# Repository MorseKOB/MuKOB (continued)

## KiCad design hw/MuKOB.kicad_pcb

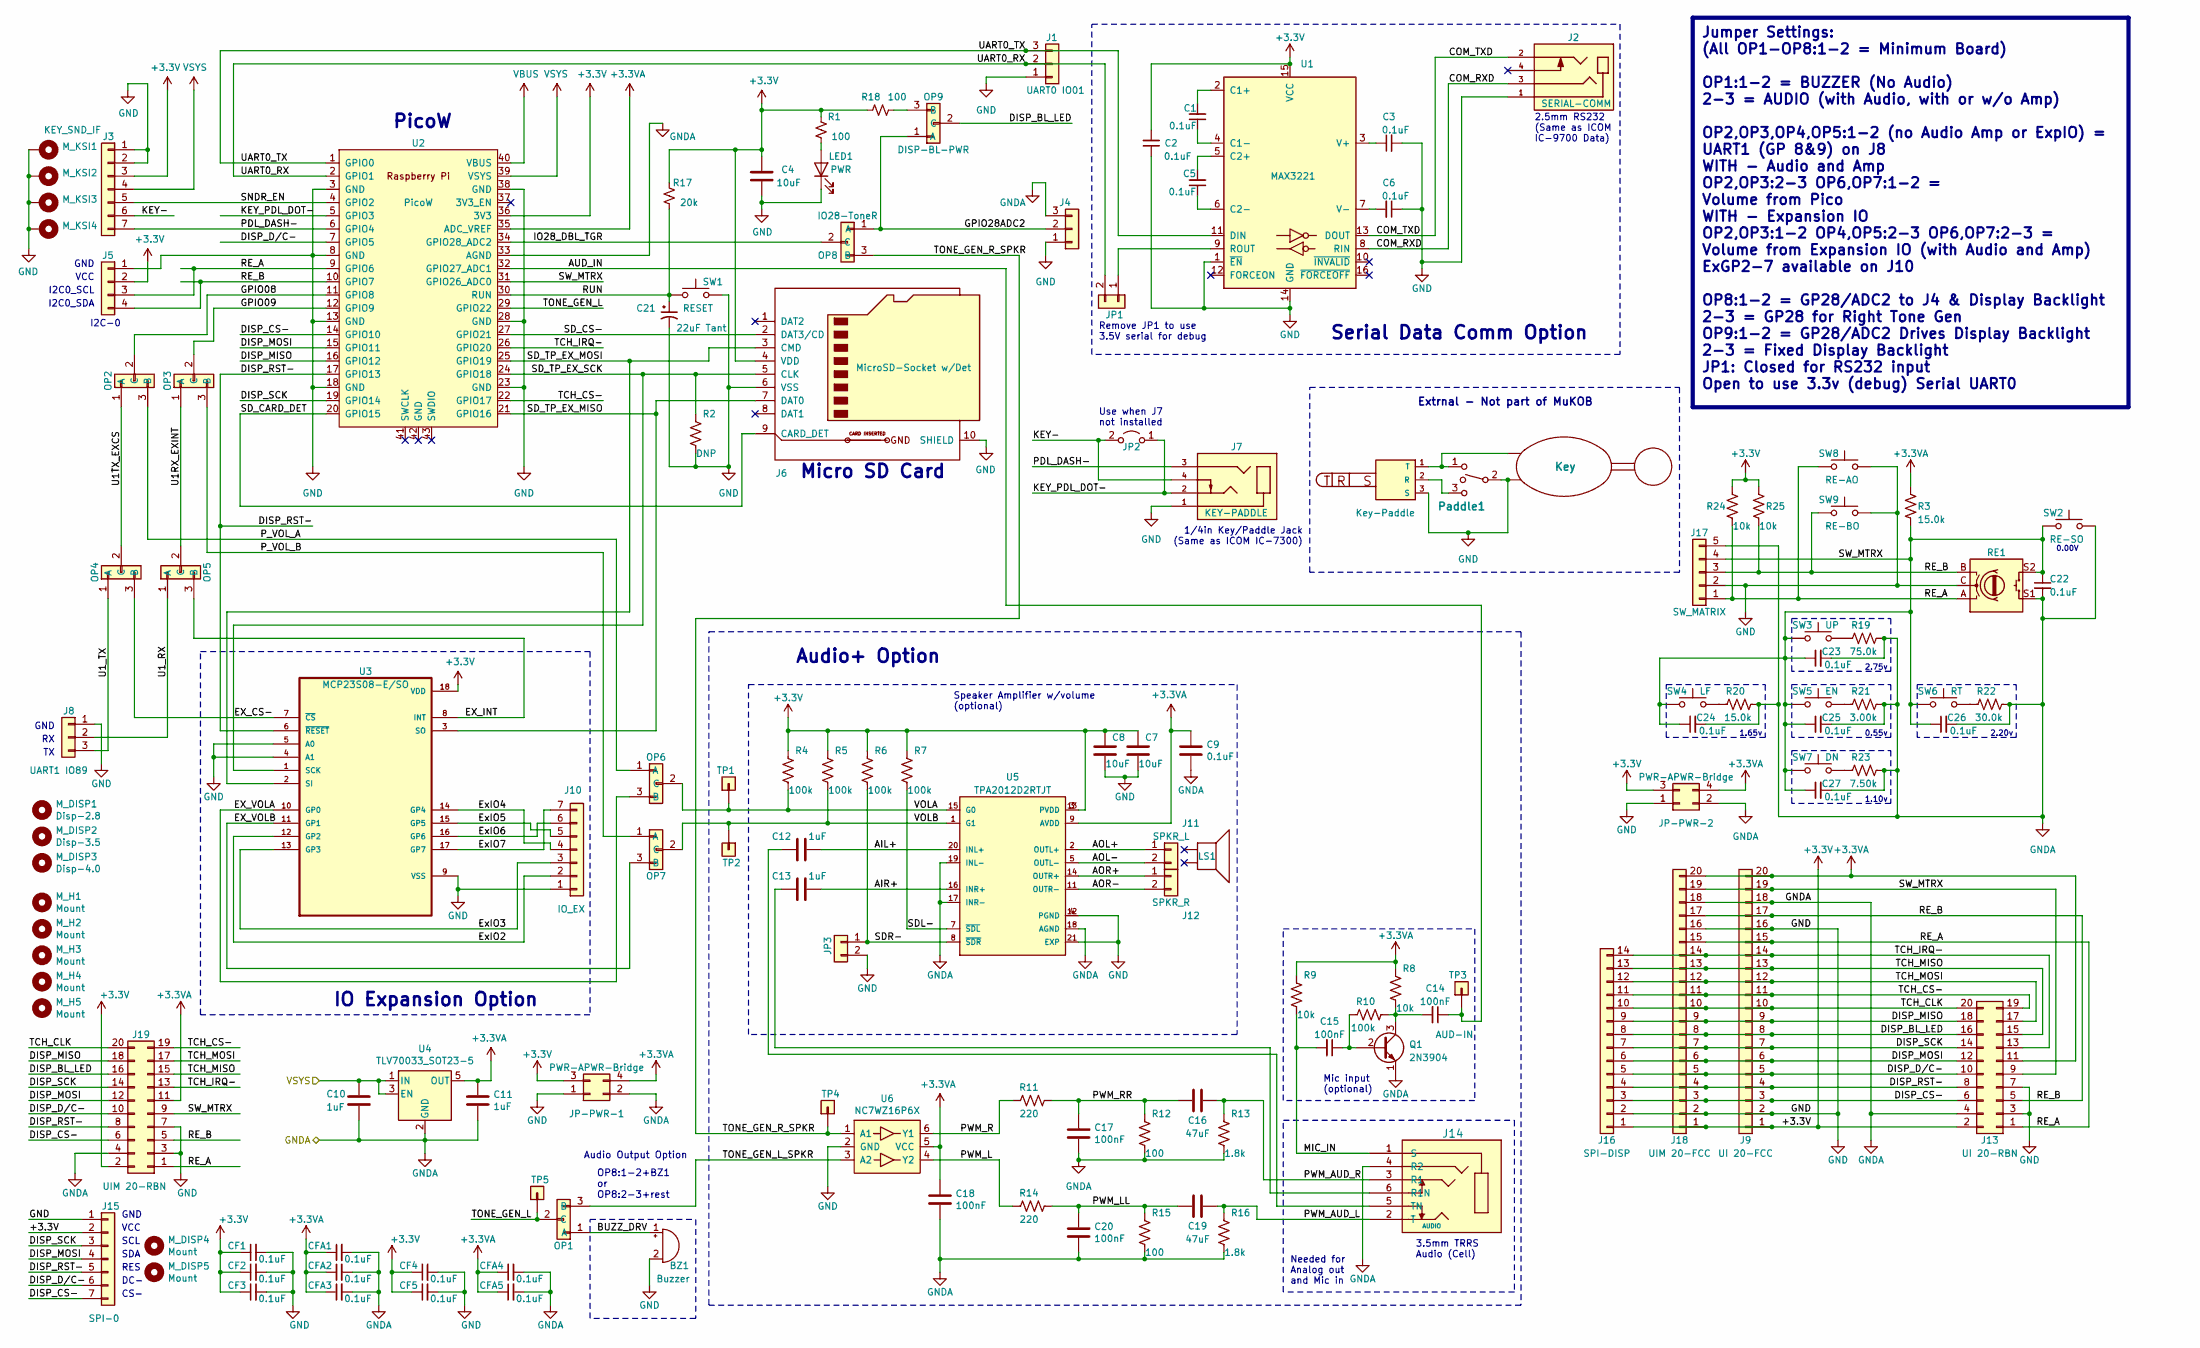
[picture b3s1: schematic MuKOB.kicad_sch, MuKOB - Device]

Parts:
BZ1: Buzzer; Buzzer_12x9.5RM7.6
C1, C2, C3, C5, C6, C9, C22, C23, C24, C25, C26, C27: 0.1uF; C_0603_1608Metric_Pad1.08x0.95mm_HandSolder
C4, C7, C8: 10uF; C_0603_1608Metric
C10, C11, C12, C13: 1uF; C_0201_0603Metric_Pad0.64x0.40mm_HandSolder
C14, C15, C17, C18, C20: 100nF; C_0201_0603Metric_Pad0.64x0.40mm_HandSolder
C16, C19: 47uF; C_1206_3216Metric_Pad1.33x1.80mm_HandSolder
C21: 22uF Tant; CP_EIA-3528-15_AVX-H_Pad1.50x2.35mm_HandSolder
CF1, CF2, CF3, CF4, CF5: 0.1uF; C_Axial_L3.8mm_D2.6mm_P7.50mm_Horizontal
CFA1, CFA2, CFA3, CFA4, CFA5: 0.1uF; C_Axial_L3.8mm_D2.6mm_P7.50mm_Horizontal
J1: UART0 IO01; PinHeader_1x03_P2.54mm_Vertical
J2: SERIAL-COMM; CUI_SJ-2524-SMT-TRS-audio-jack; PARTREV 1.05
J3: KEY_SND_IF; PinSocket_1x07_P2.54mm_Vertical
J4: GPIO28; PinHeader_1x03_P2.54mm_Vertical
J5: I2C-0; PinSocket_1x04_P2.54mm_Vertical
J6: MicroSD-Socket w/Det; SDCard-GCT_MEM2075-00-140-01-A
J7: KEY-PADDLE; CUI_SJ-63063B-audio-jack; PARTREV 1.0
J8: UART1 IO89; PinHeader_1x03_P2.54mm_Vertical
J9: UI 20-FCC; Amphenol_F51L_1x20_P1.00mm_Horizontal-FFC
J10: IO_EX; PinHeader_1x07_P2.54mm_Vertical
J11: SPKR_L; TerminalBlock_Philmore_TB132_1x02_P5.00mm_Horizontal
J12: SPKR_R; TerminalBlock_Philmore_TB132_1x02_P5.00mm_Horizontal
J13: UI 20-RBN; PinHeader_2x10_P2.54mm_Vertical
J14: AUDIO; CUI_DEVICES_SJ43516_SMT-CPJ
J15: SPI-0; PinSocket_1x07_P2.54mm_Vertical
J16: SPI-DISP; PinSocket_1x14_P2.54mm_Vertical
J17: SW_MATRIX; PinHeader_1x05_P2.54mm_Vertical
J18: UIM 20-FCC; Amphenol_F51L_1x20_P1.00mm_Horizontal-FFC
J19: UIM 20-RBN; PinHeader_2x10_P2.54mm_Vertical
J-SP1: Key-Paddle
JP1: S0-RX; PinHeader_1x02_P2.54mm_Vertical
JP2: J7-BP; PinHeader_1x02_P2.54mm_Vertical
JP3: AUD-SDR-; PinHeader_1x02_P2.54mm_Vertical
JP-PWR-1, JP-PWR-2: PWR-APWR-Bridge; PinHeader_2x02_P2.54mm_Vertical
KEY-EXT1: Key
LED1: PWR; LED_SMD_SIDEVIEW_Harvatek
LS1: Speaker
M_DISP1: Disp-2.8; MountingHole_3.2mm_M3
M_DISP2: Disp-3.5; MountingHole_3.2mm_M3
M_DISP3: Disp-4.0; MountingHole_3.2mm_M3
M_DISP4, M_DISP5: Mount; MountingHole_2.7mm_M2.5
M_H1, M_H2, M_H3, M_H4, M_H5: Mount; MountingHole_3.2mm_M3_ISO7380
M_KSI1, M_KSI2, M_KSI3, M_KSI4: MountingHole_Pad; MountingHole_3.2mm_M3_ISO7380_Pad_TopBottom
OP1: BZ-SPK; PinHeader_1x03_P2.54mm_Vertical
OP2, OP3, OP4, OP5, OP6, OP7: OP_A-B; PinHeader_1x03_P2.54mm_Vertical
OP8: IO28-ToneR; PinHeader_1x03_P2.54mm_Vertical
OP9: DISP-BL-PWR; PinHeader_1x03_P2.54mm_Vertical
Paddle1: PDL_EXT
Q1: 2N3904; TO-92_Inline
R1, R12, R15, R18: 100; R_0402_1005Metric_Pad0.72x0.64mm_HandSolder
R2: DNP; R_Axial_DIN0207_L6.3mm_D2.5mm_P10.16mm_Horizontal
R3, R20: 15.0k; R_0402_1005Metric_Pad0.72x0.64mm_HandSolder
R4, R5, R6, R7, R10: 100k; R_0402_1005Metric_Pad0.72x0.64mm_HandSolder
R8, R9, R24, R25: 10k; R_0402_1005Metric_Pad0.72x0.64mm_HandSolder
R11, R14: 220; R_0402_1005Metric_Pad0.72x0.64mm_HandSolder
R13, R16: 1.8k; R_0402_1005Metric_Pad0.72x0.64mm_HandSolder
R17: 20k; R_0402_1005Metric_Pad0.72x0.64mm_HandSolder
R19: 75.0k; R_0402_1005Metric_Pad0.72x0.64mm_HandSolder
R21: 3.00k; R_0402_1005Metric_Pad0.72x0.64mm_HandSolder
R22: 30.0k; R_0402_1005Metric_Pad0.72x0.64mm_HandSolder
R23: 7.50k; R_0402_1005Metric_Pad0.72x0.64mm_HandSolder
RE1: RotEnc-SW; RotaryEncoder_Bourns_Vertical_PEC12R-3xxxF-Sxxxx
SW1: RESET; SW_PUSH_SMD_1P1T_NO_45x45mm-CK
SW2: RE-SO; SW_PUSH_SMD_1P1T_NO_45x45mm-CK
SW3: UP; SW_PUSH_SMD_1P1T_NO_45x45mm-CK
SW4: LF; SW_PUSH_SMD_1P1T_NO_45x45mm-CK
SW5: EN; SW_PUSH_SMD_1P1T_NO_45x45mm-CK
SW6: RT; SW_PUSH_SMD_1P1T_NO_45x45mm-CK
SW7: DN; SW_PUSH_SMD_1P1T_NO_45x45mm-CK
SW8: RE-AO; SW_PUSH_SMD_1P1T_NO_45x45mm-CK
SW9: RE-BO; SW_PUSH_SMD_1P1T_NO_45x45mm-CK
TP1: VOL-A; PinHeader_1x01_P2.54mm_Vertical
TP2: VOL-B; PinHeader_1x01_P2.54mm_Vertical
TP3: AUD-IN; PinHeader_1x01_P2.54mm_Vertical
TP4: TONE-R; PinHeader_1x01_P2.54mm_Vertical
TP5: TONE-L; PinHeader_1x01_P2.54mm_Vertical
U1: MAX3221; TSSOP-16
U2: PicoW; RPi_PicoW_SMD_TH
U3: MCP23S08-E/SO; SOIC-18W_7.5x11.6mm_P1.27mm
U4: TLV70033_SOT23-5; SOT-23-5
U5: TPA2012D2RTJT; QFN50P400X400X80-21N270X270; PARTREV NA
U6: NC7WZ16P6X; SOT-363_SC-70-6

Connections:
+3.3V: C2.2, C4.1, C7.1, C8.1, CF1.1, CF2.1, CF3.1, CF4.1, CF5.1, J3.3, J5.2, J6.4 (VDD), J9.1, J13.2, J15.2, J16.1, J18.1, J19.2, JP-PWR-1.3, JP-PWR-2.3, R1.1, R4.1, R5.1, R6.1, R7.1, R17.1, R18.1, R24.1, R25.1, U1.15 (VCC), U2.36 (3V3), U3.18 (VDD), U5.3 (PVDD), U5.13 (PVDD)
+3.3VA: C9.1, C11.1, C18.1, CFA1.1, CFA2.1, CFA3.1, CFA4.1, CFA5.1, J9.20, J13.11, J18.20, J19.11, JP-PWR-1.4, JP-PWR-2.4, R3.1, R8.1, R9.1, U2.35 (ADC_VREF), U4.5 (OUT), U5.9 (AVDD), U6.5 (VCC)
/AIL+: C12.1, U5.20 (INL+)
/AIR+: C13.1, U5.16 (INR+)
/AOL+: J11.1, U5.2 (OUTL+)
/AOL-: J11.2, U5.5 (OUTL-)
/AOR+: J12.1, U5.14 (OUTR+)
/AOR-: J12.2, U5.11 (OUTR-)
/AUD_IN: C14.1, TP3.1, U2.32 (GPIO27_ADC1)
/BUZZ_DRV: BZ1.1 (-), OP1.1 (A)
/COM_RXD: J2.3, U1.8 (RIN)
/COM_TXD: J2.2, U1.13 (DOUT)
/DISP_BL_LED: J9.8, J13.16, J16.8, J18.8, J19.16, OP9.2 (C)
/DISP_CS-: J9.3, J13.6, J15.7, J16.3, J18.3, J19.6, U2.14 (GPIO10)
/DISP_D/C-: J9.5, J13.10, J15.6, J16.5, J18.5, J19.10, U2.7 (GPIO5)
/DISP_MISO: J9.9, J13.18, J16.9, J18.9, J19.18, U2.16 (GPIO12)
/DISP_MOSI: J9.6, J13.12, J15.4, J16.6, J18.6, J19.12, U2.15 (GPIO11)
/DISP_RST-: J9.4, J13.8, J15.5, J16.4, J18.4, J19.8, U2.17 (GPIO13), U3.6 (~RESET)
/DISP_SCK: J9.7, J13.14, J15.3, J16.7, J18.7, J19.14, U2.19 (GPIO14)
/EX_CS-: OP4.3 (B), U3.7 (~CS)
/EX_INT: OP5.3 (B), U3.8 (INT)
/EX_VOLA: OP6.3 (B), U3.10 (GP0)
/EX_VOLB: OP7.3 (B), U3.11 (GP1)
/ExIO2: J10.2, U3.12 (GP2)
/ExIO3: J10.3, U3.13 (GP3)
/ExIO4: J10.4, U3.14 (GP4)
/ExIO5: J10.5, U3.15 (GP5)
/ExIO6: J10.6, U3.16 (GP6)
/ExIO7: J10.7, U3.17 (GP7)
/GPIO08: OP2.2 (C), U2.11 (GPIO8)
/GPIO09: OP3.2 (C), U2.12 (GPIO9)
/GPIO28ADC2: J4.2, OP8.1 (A), OP9.1 (A)
/IO28_DBL_TGR: OP8.2 (C), U2.34 (GPIO28_ADC2)
/KEY-: J3.6, J7.4, JP2.2 (B)
/KEY_PDL_DOT-: J7.2, JP2.1 (A), U2.5 (GPIO3)
/MIC_IN: C15.2, J14.1 (S), R9.2
/PDL_DASH-: J3.7, J7.3, U2.6 (GPIO4)
/PWM_AUD_L: C19.1, J14.2 (T), R16.1
/PWM_AUD_R: C16.1, J14.3 (R1), R13.1
/PWM_L: R14.2, U6.4 (Y2)
/PWM_LL: C19.2, C20.1, R14.1, R15.1
/PWM_R: R11.2, U6.6 (Y1)
/PWM_RR: C16.2, C17.1, R11.1, R12.1
/P_VOL_A: OP2.3 (B), OP6.1 (A)
/P_VOL_B: OP3.3 (B), OP7.1 (A)
/RE_A: J5.3, J9.15, J13.1, J17.1, J18.15, J19.1, R24.2, RE1.A, SW8.1, U2.9 (GPIO6)
/RE_B: J5.4, J9.17, J13.5, J17.3, J18.17, J19.5, R25.2, RE1.B, SW9.1, U2.10 (GPIO7)
/RUN: C21.1, R17.2, SW1.1, U2.30 (RUN)
/SDL-: R7.2, U5.7 (~SDL)
/SDR-: JP3.1, R6.2, U5.8 (~SDR)
/SD_CARD_DET: J6.9 (CARD_DET), U2.20 (GPIO15)
/SD_CS-: J6.2 (DAT3/CD), U2.27 (GPIO21)
/SD_TP_EX_MISO: J6.7 (DAT0), U2.21 (GPIO16), U3.3 (SO)
/SD_TP_EX_SCK: J6.5 (CLK), J-SP1.1 (T), Paddle1.1, R2.1, U2.24 (GPIO18), U3.1 (SCK)
/SNDR_EN: J3.5, U2.4 (GPIO2)
/SW_MTRX: C22.1, C23.1, C24.1, C25.1, C26.1, C27.1, J9.19, J13.9, J17.4, J18.19, J19.9, R3.2, RE1.S2, SW2.1, SW3.1, SW4.1, SW5.1, SW6.1, SW7.1, U2.31 (GPIO26_ADC0)
/TCH_CLK: J9.10, J13.20, J16.10, J18.10, J19.20
/TCH_CS-: J9.11, J13.19, J16.11, J18.11, J19.19, U2.22 (GPIO17)
/TCH_IRQ-: J9.14, J13.13, J16.14, J18.14, J19.13, U2.26 (GPIO20)
/TCH_MISO: J9.13, J13.15, J16.13, J18.13, J19.15
/TCH_MOSI: J9.12, J13.17, J16.12, J18.12, J19.17
/TONE_GEN_L: OP1.2 (C), TP5.1, U2.29 (GPIO22)
/TONE_GEN_L_SPKR: OP1.3 (B), U6.3 (A2)
/TONE_GEN_R_SPKR: OP8.3 (B), TP4.1, U6.1 (A1)
/U1RX_EXINT: OP3.1 (A), OP5.2 (C)
/U1TX_EXCS: OP2.1 (A), OP4.2 (C)
/U1_RX: J8.2, OP5.1 (A)
/U1_TX: J8.3, OP4.1 (A)
/UART0_RX: J1.2, JP1.2, U2.2 (GPIO1)
/UART0_TX: J1.3, U1.11 (DIN), U2.1 (GPIO0)
/VOLA: OP6.2 (C), R4.2, TP1.1, U5.15 (G0)
/VOLB: OP7.2 (C), R5.2, TP2.1, U5.1 (G1)
GNDA: C9.2, C10.2, C11.2, C17.2, C18.2, C20.2, C22.2, C23.2, C24.2, C25.2, C26.2, C27.2, CFA1.2, CFA2.2, CFA3.2, CFA4.2, CFA5.2, J4.3, J9.18, J13.4, J14.4 (R2), J17.5, J18.18, J19.4, JP-PWR-1.2, JP-PWR-2.2, Q1.1 (E), R12.2, R13.2, R15.2, R16.2, R19.1, R20.1, R21.1, R22.1, R23.1, RE1.S1, SW2.2, U2.33 (AGND), U4.2 (GND), U5.17 (INR-), U5.18 (AGND), U5.19 (INL-)
unnamed: C13.2, J14.6 (R1N)
unnamed: C12.2, J14.5 (TN)
unnamed: J-SP1.2 (R), Paddle1.3
unnamed: JP1.1, U1.9 (ROUT)
unnamed: LED1.2 (A), R1.2
unnamed: OP9.3 (B), R18.2
unnamed: C15.1, Q1.2 (B), R10.2
unnamed: C14.2, Q1.3 (C), R8.2, R10.1
unnamed: R19.2, SW3.2
unnamed: R20.2, SW4.2
unnamed: R21.2, SW5.2
unnamed: R22.2, SW6.2
unnamed: R23.2, SW7.2
unnamed: C1.2, U1.2 (C1+)
unnamed: C1.1, U1.4 (C1-)
unnamed: C5.2, U1.5 (C2+)
unnamed: C5.1, U1.6 (C2-)
unnamed: C3.1, U1.3 (V+)
unnamed: C6.2, U1.7 (V-)
VBUS: U2.40 (VBUS)
VSYS: C10.1, J3.4, U2.39 (VSYS), U4.1 (IN), U4.3 (EN)

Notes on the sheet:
Jumper Settings: (All OP1-OP8:1-2 = Minimum Board) OP1:1-2 = BUZZER (No Audio) 2-3 = AUDIO (with Audio, with or w/o Amp) OP2,OP3,OP4,OP5:1-2 (no Audio Amp or ExpIO) = UART1 (GP 8&9) on J8 WITH - Audio and Amp OP2,OP3:2-3 OP6,OP7:1-2 = Volume from Pico WITH - Expansion IO OP2,OP3:1-2 OP4,OP5:2-3 OP6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
DC-
2.20v
RES
SCL
Speaker Amplifier w/volume (optional)
GND
Remove JP1 to use 3.5V serial for debug
1.10v
VCC
I2C-0
Audio+ Option
PicoW
0.55v
2.75v
CS-
SDA
3.5mm TRRS Audio (Cell)
Audio Output Option
OP8:1-2+BZ1 or OP8:2-3+rest
2.5mm RS232 (Same as ICOM IC-9700 Data)
Needed for Analog out and Mic in
I2C0_SDA
Serial Data Comm Option
Micro SD Card
Use when J7 not installed
Extrnal - Not part of MuKOB
Mic input (optional)
1.65v
1/4in Key/Paddle Jack (Same as ICOM IC-7300)
IO Expansion Option
I2C0_SCL
0.00V

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
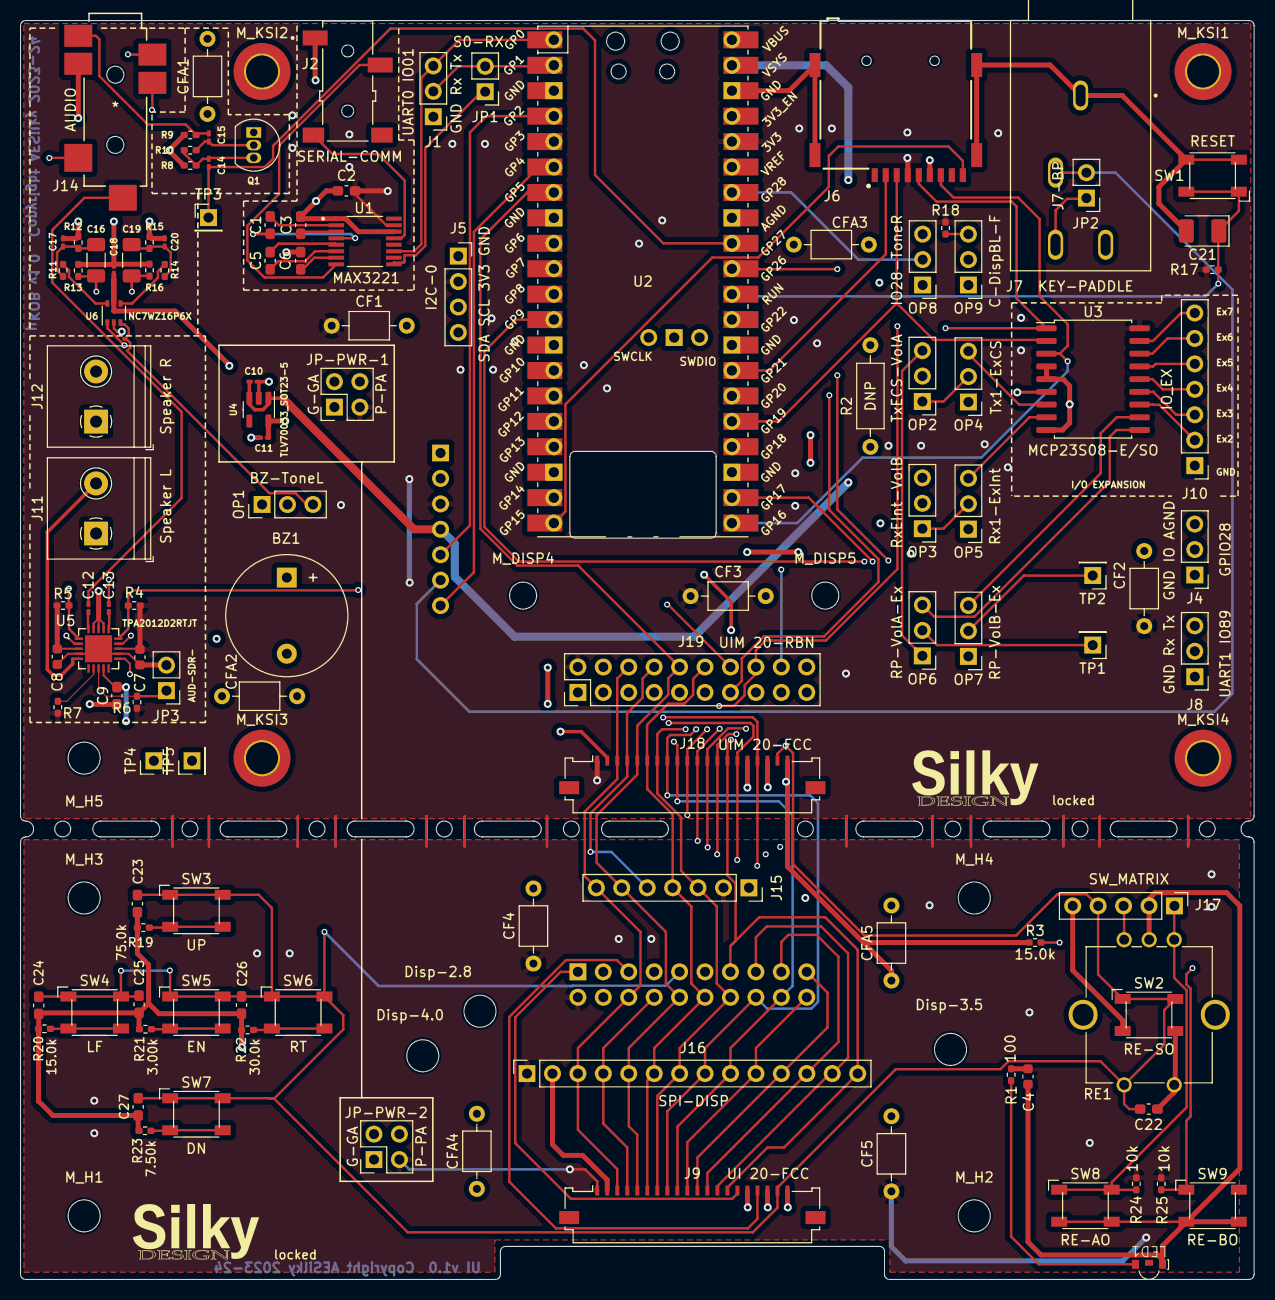
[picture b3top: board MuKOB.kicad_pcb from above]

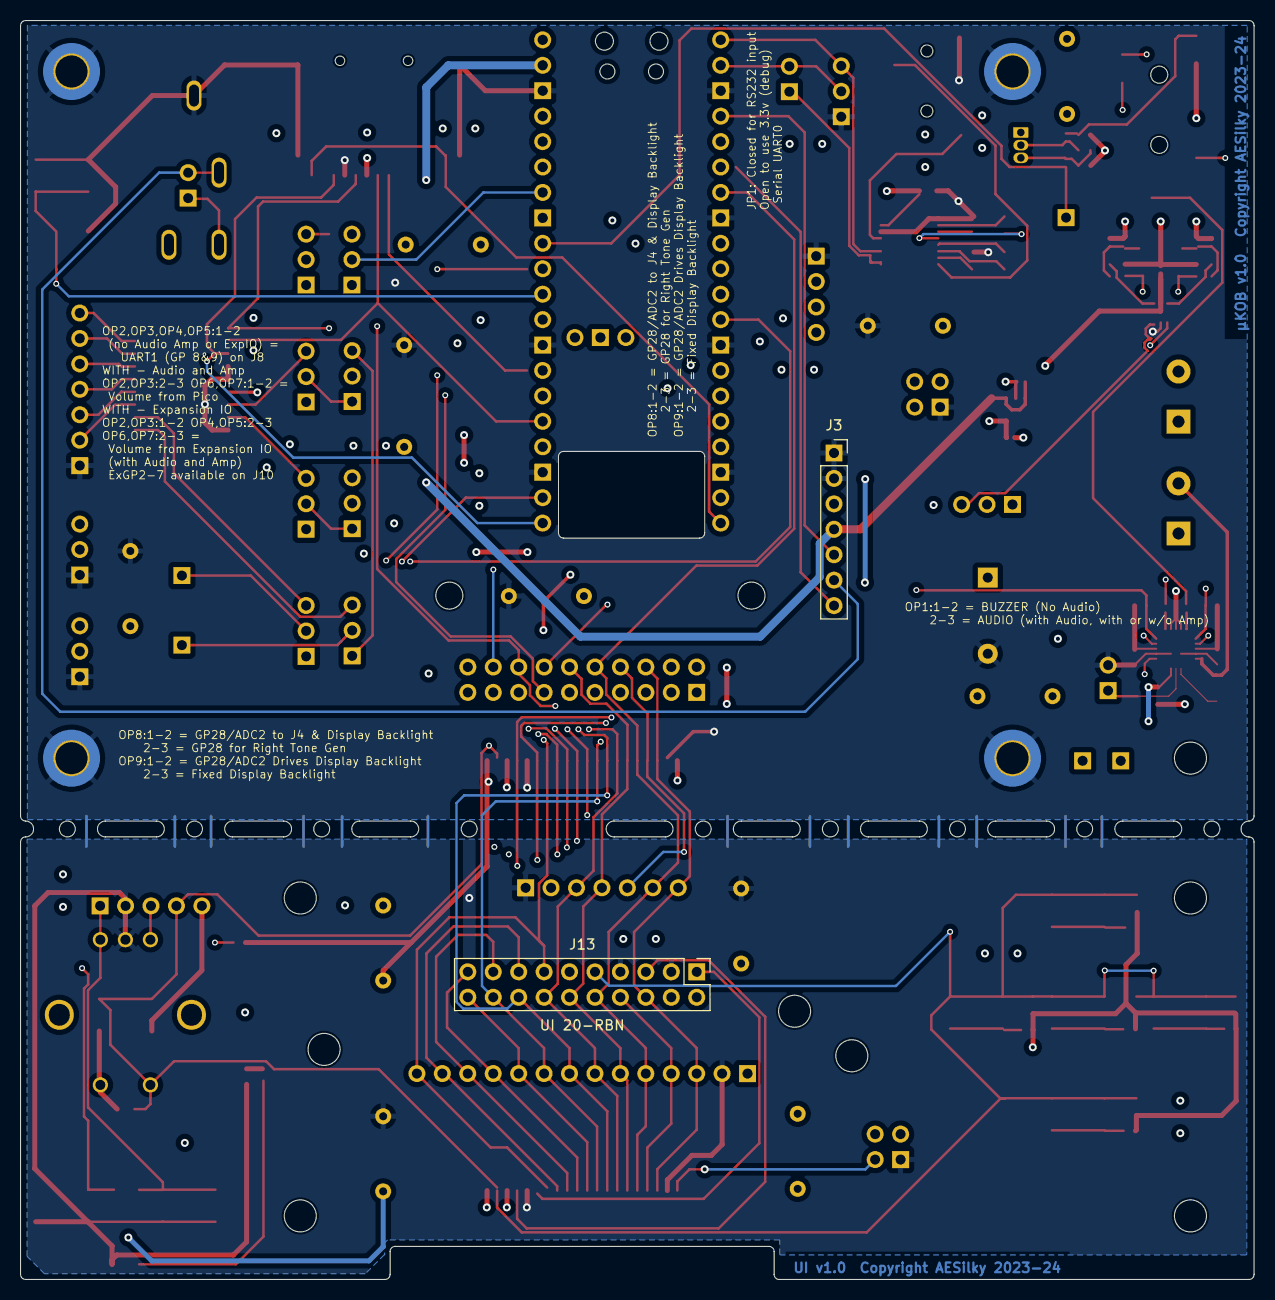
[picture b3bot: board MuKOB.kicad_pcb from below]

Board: 4 copper layers, 123.2 x 125.7 mm, 135 parts (2 on the bottom side), 94 nets.

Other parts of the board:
G1, G2: LOGO; SILKY-DESIGN-logo-0_50-AES

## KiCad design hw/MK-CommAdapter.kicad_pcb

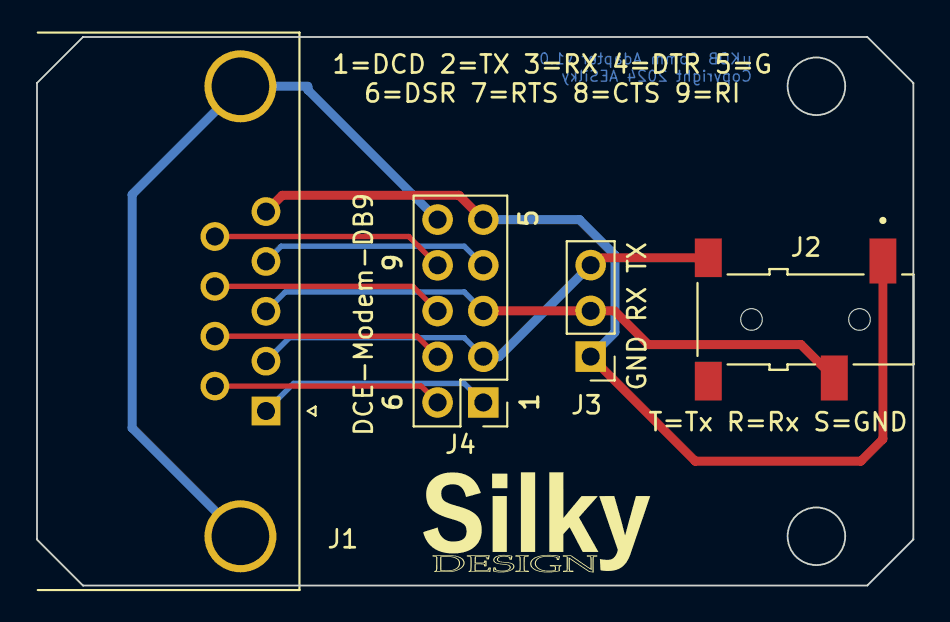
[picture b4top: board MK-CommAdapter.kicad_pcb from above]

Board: 2 copper layers, 48.7 x 30.5 mm, 4 parts (0 on the bottom side), 10 nets.

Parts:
J1: DCE-Modem-DB9; DSUB-9_Female_Horizontal_P2.77x2.84mm_EdgePinOffset9.90mm_H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
J2: MuKOB-COMM; CUI_SJ-2524-SMT-TRS-audio-jack
J3: COMM-3; PinHeader_1x03_P2.54mm_Vertical
J4: COMM-DCE-10; PinHeader_2x05_DB9-Order

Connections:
/CH-GND: J1.0 (PAD), J4.10
/CTS: J1.8, J4.8
/DCD: J1.1, J4.1
/DSR: J1.6, J4.6
/DTR: J1.4, J4.4
/RI: J1.9, J4.9
/RTS: J1.7, J4.7
/RXD: J1.3, J2.3, J3.2, J4.3
/TXD: J1.2, J2.2, J3.3, J4.2
GND: J1.5, J2.1, J3.1, J4.5

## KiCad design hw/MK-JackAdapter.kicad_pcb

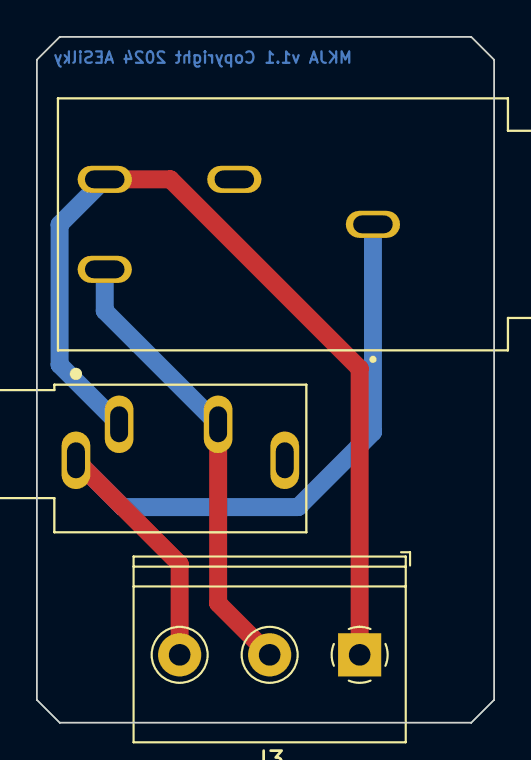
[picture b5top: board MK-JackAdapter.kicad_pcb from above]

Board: 2 copper layers, 25.4 x 38.1 mm, 3 parts (0 on the bottom side), 3 nets.

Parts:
J1: KEY-PADDLE-4; CUI_SJ-63063B-audio-jack
J2: KEY-PADDLE-8; CUI_SJ1-3534NG-audio-jack
J3: Screw_Terminal_01x03; TerminalBlock_Philmore_TB133_1x03_P5.00mm_Horizontal

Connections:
/COMMON: J1.1, J2.1, J3.3
/KEY_PDL_DOT-: J1.2, J2.2, J3.1
/PDL_DASH-: J1.3, J2.3, J3.2

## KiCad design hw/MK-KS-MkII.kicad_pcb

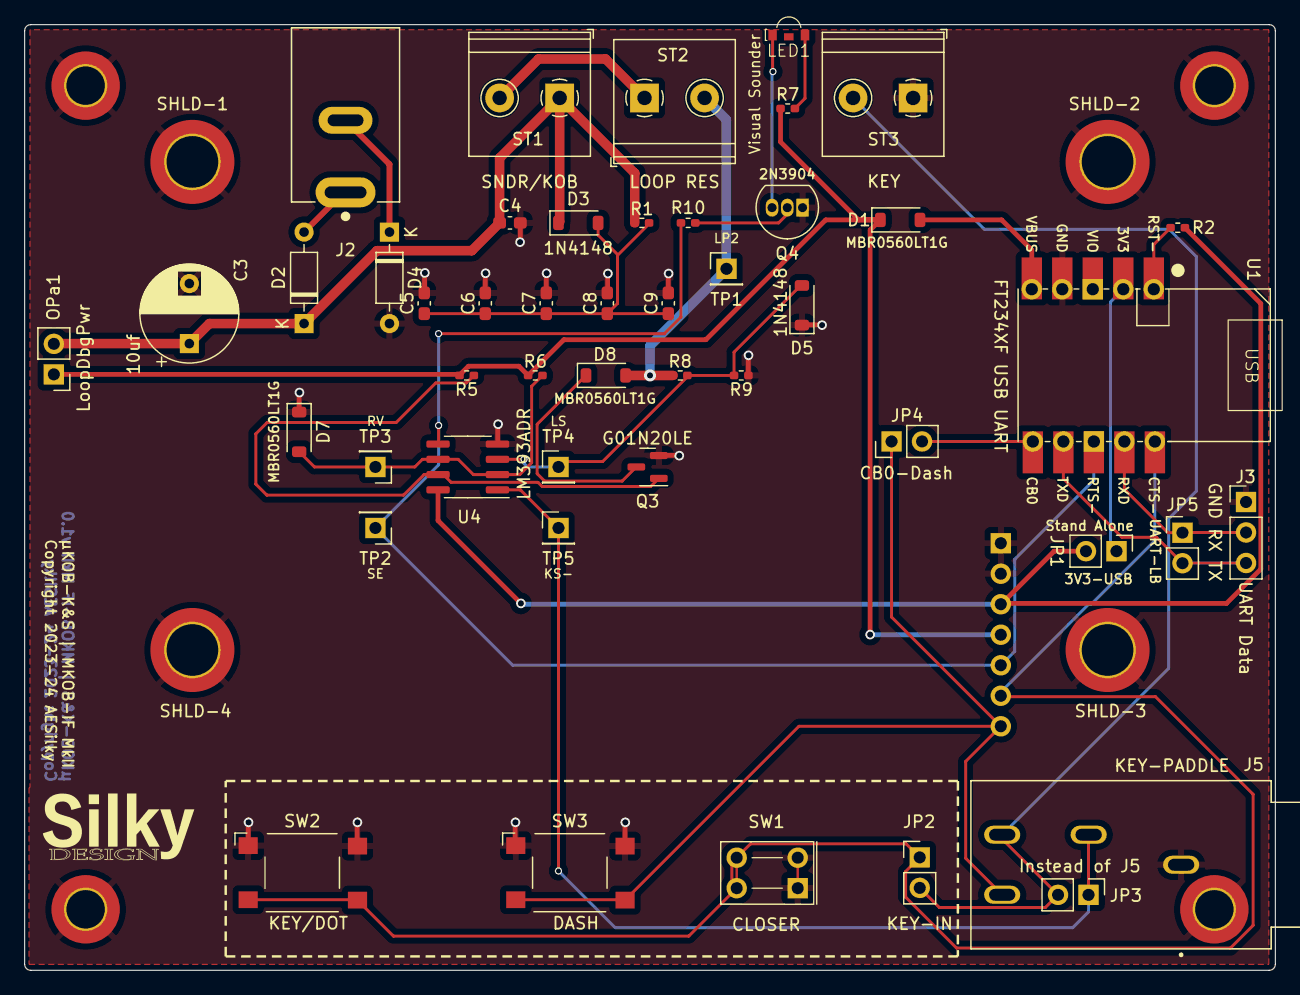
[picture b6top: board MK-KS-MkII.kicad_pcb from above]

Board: 2 copper layers, 104.1 x 78.7 mm, 57 parts (1 on the bottom side), 27 nets.

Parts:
C3: 10uf; CP_Radial_D8.0mm_P5.00mm
C4, C5, C6, C7, C8, C9: 0.1u; C_0603_1608Metric_Pad1.08x0.95mm_HandSolder
D1, D7, D8: MBR0560LT1G; D_SOD-123
D2, D4: 1N4148; D_DO-35_SOD27_P7.62mm_Horizontal
D3, D5: 1N4148; D_SOD-123
G1: LOGO; SILKY-DESIGN-logo-0_50-AES
J2: LOOP PWR; AES-CUI_PJ-037B
J3: UART Data; PinHeader_1x03_P2.54mm_Vertical
J4: MuKOB IF; PinHeader_1x07_P2.54mm_Vertical
J5: KEY-PADDLE; AES-CUI_SJ-63063B-audio-jack
JP1: 3V3-USB; PinHeader_1x02_P2.54mm_Vertical
JP2: KEY-IN; PinHeader_1x02_P2.54mm_Vertical
JP3: Key Jack NP; PinHeader_1x02_P2.54mm_Vertical
JP4: CB0-Dash; PinHeader_1x02_P2.54mm_Vertical
JP5: UART-LB; PinHeader_1x02_P2.54mm_Vertical
LED1: SNDR; AES-LED_SMD_SIDEVIEW_Harvatek
M_KSI1, M_KSI2, M_KSI3, M_KSI4: MountingHole_Pad; MountingHole_3.2mm_M3_ISO7380_Pad_TopBottom
OPa1: LoopDbgPwr; PinHeader_1x02_P2.54mm_Vertical
Q3: G01N20LE; SOT-23
Q4: 2N3904; TO-92_Inline
R1: 3.3k; R_0402_1005Metric_Pad0.72x0.64mm_HandSolder
R2, R5, R6, R8: 20k; R_0402_1005Metric_Pad0.72x0.64mm_HandSolder
R7: 100; R_0402_1005Metric_Pad0.72x0.64mm_HandSolder
R9: DNP; R_0402_1005Metric_Pad0.72x0.64mm_HandSolder
R10: 1k; R_0402_1005Metric_Pad0.72x0.64mm_HandSolder
SHLD-1, SHLD-2, SHLD-3, SHLD-4: MountingHole_Pad; MountingHole_4.3mm_M4_ISO14580_Pad_TopBottom
ST1: SNDR/KOB; TerminalBlock_Philmore_TB132_1x02_P5.00mm_Horizontal
ST2: LOOP RES; TerminalBlock_Philmore_TB132_1x02_P5.00mm_Horizontal
ST3: KEY; TerminalBlock_Philmore_TB132_1x02_P5.00mm_Horizontal
SW1: CLOSER; AES-SW-TGL-Micro-DPST-CIT
SW2: KEY/DOT; AES-SW_PUSH_SMD_1P1T_NO_6x6mm
SW3: DASH; AES-SW_PUSH_SMD_1P1T_NO_6x6mm
TP1: LP2; PinHeader_1x01_P2.54mm_Vertical
TP2: SE; PinHeader_1x01_P2.54mm_Vertical
TP3: RV; PinHeader_1x01_P2.54mm_Vertical
TP4: LS; PinHeader_1x01_P2.54mm_Vertical
TP5: KS-; PinHeader_1x01_P2.54mm_Vertical
U1: FT234XF_USB_UART_Module; AES-FTDI-UMFT234XF
U4: LM393ADR; SOIC-8_3.9x4.9mm_P1.27mm

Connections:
+3.3V: J4.3, JP1.2 (B), R2.2, U4.8 (VCC)
+5V: D1.1 (K), J4.4, OPa1.1, R5.2, R6.1, R7.1
/CB0: JP4.2 (B), U1.6 (CB0)
/KEY_PDL-: J5.2, JP2.2 (B), JP3.2 (B), ST3.2
/KEY_PDL_DOT-: J4.6, JP2.1 (A), SW1.2 (B), SW2.2, U1.10 (CTS-)
/KOB_KEY-: J5.4, JP3.1 (A), TP5.1, U4.1 (1OUT)
/LOOP_PWR: C3.1, C4.1, D2.1 (K), D3.1 (K), OPa1.2, R1.1, ST1.1
/LOOP_STATE: D5.2 (A), R8.2, R9.2, TP4.1, U4.3
/LP1: ST1.2, ST2.1
/LP2: D8.2 (A), R8.1, ST2.2, TP1.1
/LPI+: D2.2 (A), J2.1 (In)
/LPI-: D4.1 (K), J2.2 (Ext)
/OFFSET_REF_V: D7.2 (A), R6.2, TP3.1, U4.2, U4.6 (2IN-)
/PDL_DASH-: J4.7, J5.3, JP4.1 (A), SW3.2
/RESET-: R2.1, U1.1 (RESET-)
/RXD: J3.2, JP5.1 (A), U1.9 (RXD)
/SNDR_EN: J4.5, R10.1, TP2.1, U1.8 (RTS-), U4.5 (2IN+)
/SNDR_EN-: Q3.1 (G), R5.1, U4.7 (2OUT)
/TXD: J3.3, JP5.2 (B), U1.7 (TXD)
/V3.3I: JP1.1 (A), U1.2 (3V3)
/V5I: D1.2 (A), U1.5 (VBUS)
GND: C3.2, C4.2, C5.2, C6.2, C7.2, C8.2, C9.2, D4.2 (A), D5.1 (K), D7.1 (K), J3.1, J4.1, J4.2, J5.1, M_KSI1.1, M_KSI2.1, M_KSI3.1, M_KSI4.1, Q3.2 (S), Q4.1 (E), R9.1, SHLD-1.1, SHLD-2.1, SHLD-3.1, SHLD-4.1, ST3.1, SW1.1 (A), SW2.1, SW3.1, U1.4 (GND), U4.4 (GND)
unnamed: C5.1, C6.1, C7.1, C8.1, C9.1, D3.2 (A), R1.2
unnamed: D8.1 (K), Q3.3 (D)
unnamed: LED1.2 (A), R7.2
unnamed: LED1.1 (K), Q4.3 (C)
unnamed: Q4.2 (B), R10.2

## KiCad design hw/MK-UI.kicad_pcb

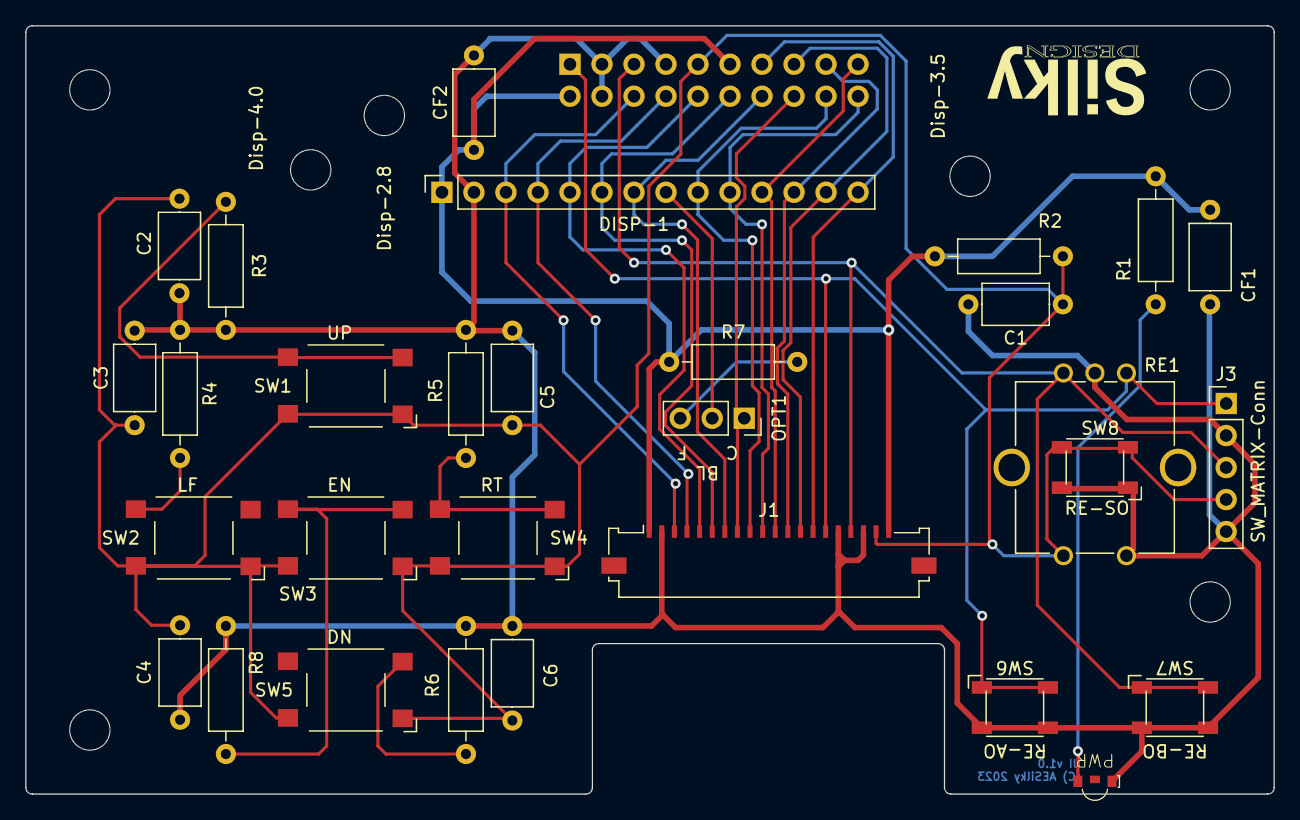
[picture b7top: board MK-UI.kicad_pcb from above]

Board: 2 copper layers, 99.1 x 61.0 mm, 38 parts (1 on the bottom side), 25 nets.

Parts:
C1, C2, C3, C4, C5, C6: 0.1uF; C_Axial_L5.1mm_D3.1mm_P7.50mm_Horizontal
CF1, CF2: 0.1uF; C_Axial_L5.1mm_D3.1mm_P7.50mm_Horizontal
DISP-1: TFT-SPI w/Touch 9/5; PinSocket_1x14_P2.54mm_Vertical
H1, H2, H3, H4: MountingHole; MountingHole_3.2mm_M3
J1: Conn_01x20-FFC; Amphenol_F51L_1x20_P1.00mm_Horizontal-FFC
J2: UI 20-RBN; PinHeader_2x10_P2.54mm_Vertical
J3: SW_MATRIX-Conn; PinHeader_1x05_P2.54mm_Vertical
LED1: PWR; LED_SMD_SIDEVIEW_Harvatek
M_DISP1: Disp-2.8; MountingHole_3.2mm_M3
M_DISP2: Disp-3.5; MountingHole_3.2mm_M3
M_DISP3: Disp-4.0; MountingHole_3.2mm_M3
OPT1: Conn_01x03; PinSocket_1x03_P2.54mm_Vertical
R1, R7: 100; R_Axial_DIN0207_L6.3mm_D2.5mm_P10.16mm_Horizontal
R2: 10k; R_Axial_DIN0207_L6.3mm_D2.5mm_P10.16mm_Horizontal
R3: 47k; R_Axial_DIN0207_L6.3mm_D2.5mm_P10.16mm_Horizontal
R4: 15k; R_Axial_DIN0207_L6.3mm_D2.5mm_P10.16mm_Horizontal
R5: 28k; R_Axial_DIN0207_L6.3mm_D2.5mm_P10.16mm_Horizontal
R6: 6.8k; R_Axial_DIN0207_L6.3mm_D2.5mm_P10.16mm_Horizontal
R8: 2.2k; R_Axial_DIN0207_L6.3mm_D2.5mm_P10.16mm_Horizontal
RE1: RotEnc-SW; RotaryEncoder_Bourns_Vertical_PEC12R-3xxxF-Sxxxx
SW1: UP; SW_PUSH_SMD_1P1T_NO_6x6mm
SW2: LF; SW_PUSH_SMD_1P1T_NO_6x6mm
SW3: EN; SW_PUSH_SMD_1P1T_NO_6x6mm
SW4: RT; SW_PUSH_SMD_1P1T_NO_6x6mm
SW5: DN; SW_PUSH_SMD_1P1T_NO_6x6mm
SW6: RE-AO; SW_PUSH_SMD_1P1T_NO_45x45mm-CK
SW7: RE-BO; SW_PUSH_SMD_1P1T_NO_45x45mm-CK
SW8: RE-SO; SW_PUSH_SMD_1P1T_NO_45x45mm-CK

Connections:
+3.3V: CF1.1, CF2.1, DISP-1.1 (VCC), J1.1, J1.20, J2.2, J2.11, R1.1, R2.1, R7.1
/DISP_BL_LED: J1.8, J2.16, OPT1.1
/DISP_CS-: DISP-1.3 (CS-), J1.3, J2.6
/DISP_D/C-: DISP-1.5 (D/C-), J1.5, J2.10
/DISP_MISO: DISP-1.9 (MISO_SDO), J1.9, J2.18
/DISP_MOSI: DISP-1.6 (MOSI_SDI), J1.6, J2.12
/DISP_RST-: DISP-1.4 (RESET-), J1.4, J2.8
/DISP_SCK: DISP-1.7 (SCK), J1.7, J2.14
/RE_A: J1.15, J2.1, J3.1, RE1.A, SW6.1
/RE_B: J1.17, J2.5, J3.3, RE1.B, SW7.1
/SW_MTRX: C1.1, C2.1, C3.1, C4.1, C5.1, C6.1, J1.19, J2.9, J3.4, R2.2, RE1.S2, SW1.1, SW2.1, SW3.1, SW4.1, SW5.1, SW8.2
/TCH_CLK: DISP-1.10 (T_CLK), J1.10, J2.20
/TCH_CS-: DISP-1.11 (T_CS-), J1.11, J2.19
/TCH_IRQ-: DISP-1.14 (T_IRQ), J1.14, J2.13
/TCH_MISO: DISP-1.13 (T_DO), J1.13, J2.15
/TCH_MOSI: DISP-1.12 (T_DIN), J1.12, J2.17
GND: C1.2, C2.2, C3.2, C4.2, C5.2, C6.2, CF1.2, CF2.2, DISP-1.2 (GND), J1.2, J1.16, J1.18, J2.3, J2.4, J2.7, J3.2, J3.5, LED1.1 (K), R3.1, R4.1, R5.1, R6.1, R8.1, RE1.C, RE1.S1, SW6.2, SW7.2, SW8.1
unnamed: DISP-1.8 (LED_BL), OPT1.2
unnamed: LED1.2 (A), R1.2
unnamed: OPT1.3, R7.2
unnamed: R3.2, SW1.2
unnamed: R4.2, SW2.2
unnamed: R5.2, SW4.2
unnamed: R6.2, SW5.2
unnamed: R8.2, SW3.2

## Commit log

2023-01-22 START
2023-01-22 Change font special chars. Exclude 'build'.
2023-01-23 Font - Through capitals done.
2023-01-23 Separate out OLED graphics operations and text display operations.
2023-01-24 Display functional (display chars/strings, scroll, etc.)
2023-01-24 Updates to printing strings.
2023-01-24 Fix font (too many cols in 1 char). Add SP card library.
2023-01-24 Add component docs
2023-01-25 Add support for rotory encoder+switch.
2023-02-01 Reorganize source. Some board init working.
2023-02-05 VGA 16 color info.
2023-02-05 Remove duplicate files.
2023-02-06 Display functions working.
2023-02-06 VSCode updates.
2023-02-06 Replace .gitignore
2023-02-06 Remove build from repo.
2023-02-12 Display changed to 16 lines. Connection to and receive from MorseKOB Server working.
2023-02-20 Using 64k (16bit) color to improve performance. Split SPI so Display and Touch are separate.
2023-02-25 Display scroll (full/partial), and contacts (sub screens).
2023-02-27 User docs started.
2023-02-28 Terminal input (buffered) support.
2023-03-02 Terminal (ANSI/DEC) function library.
2023-03-02 Add input available callback hook.
2023-03-04 Initial KOB. Process Config.
2023-03-04 mukboard -> mkboard to match mkwire
2023-03-10 UI & BE on separate cores and CMT. UI on display.
2023-03-10 Setup and menu icons on display.
2023-03-10 Remove leading '.' from names and update sample cfg
2023-03-10 Config structure members to match PyKOB.
2023-03-11 Process all sys-config and user-config values.
2023-03-11 Initial terminal UI.
2023-03-14 Terminal UI static screen.
2023-03-14 Command processor, build input line.
2023-03-16 Terminal UI getline and CMD updates.
2023-03-19 Wire and Speed display. Build/debug on Windows.
2023-03-21 Help system in terminal UI.
2023-03-21 Connect command and connected state working.
2023-03-21 Handle 'Current Sender' info.
2023-03-29 Morse Decode working (still needs work).
2023-03-30 Pin assignments.
2023-03-30 Add the rest of the header icons to the display.
2023-03-30 Update 'pins'.
2023-04-01 Handle sender change better.
2023-04-03 Scheduled message. Break code output at space.
2023-04-03 Decode restructured and clarified.
2023-04-04 KOB key input functional.
2023-04-04 Update README.md
    Remove extra (empty) list item.
2023-04-04 Shell - add 'alias' functionality.
2023-04-06 Configure/Cfg shell command display of config.
2023-04-11 Config save/load/name/set-as-boot. Autoconnect functional.
2023-04-12 Sound code base functionality.
2023-04-12 Handle Morse KOB Server packets in msg loop handler.
2023-04-12 Start to remove sleep.
2023-04-15 Remove any of the malloc calls.
2023-04-19 VSCode settings for CMSIS debug.
2023-04-19 Static storage.
2023-04-20 Fix keep-alive timer from us to ms.
2023-04-21 Boot rom method.
2023-04-25 Station list (first cut).
2023-04-26 Station list on the display. Readme additions.
2023-04-26 Rotory encoder and switch IRQ handler. Temp connect-toggle on PBSW push.
2023-04-28 Components docs for the board. Debug flag functionality.
2023-05-01 Add 'debug' and other commands. Remove debug from option switches.
2023-05-01 Initial support for tone.
2023-05-03 Initial support for either ILI9341 or ILI9488 display.
2023-05-07 Add process status command (.ps).
2023-05-10 Include interrupt status in '.ps' command output.
2023-05-12 Term UI station list display w/dynamic resizing.
2023-05-13 Correct Term-UI when the station list adds lines.
2023-05-14 Hardware/PCB setup.
2023-05-22 Config changed so version and name are at the beginning and don't use a key.
2023-05-25 Track GERBER files so they can be part of a project release.
2023-05-28 Main and KOB schematic pages.
2023-05-29 Schematic updates.
2023-05-29 Combine symbol files.
2023-05-30 Update and organize display component docs.
2023-05-30 Add README for the display component docs.
2023-05-30 Update README for the display component docs.
2023-05-31 HW - Display FFCs.
2023-06-02 Cfg version, name, are first 2 lines (no 'key=').
2023-06-02 Finish KOB page. UI FFC on.
2023-06-02 Schematic ready for rules check.
2023-06-02 Ignore generated reports.
2023-06-02 Flip the display vertically so connector is at the bottom.
2023-06-02 Update README.md
    Update to talk more about the complete device.
2023-06-03 Update for VSCode on Ubuntu
2023-06-03 Enable USB STDIO
2023-06-10 Touch enabled.
2023-06-10 Add types to build settings.
2023-07-08 Change display backlight GPIO.
2023-10-10 Schematic prior to pulling KOB interface to separate board.
2023-10-13 Audio on main page. KeySounder Intf on separate board. Switch matrix via Resistors.
2023-10-14 Reorganize onto 3 boards. Use 20pin UI connector.
2023-11-11 Electrical checks complete.
2023-11-18 KeySounder schematic ready for PCB layout.
2023-11-27 Schematic updates. Reorg components between boards. 20 pin ribbon.
2023-11-27 UI PCB initial
2023-12-31 Device (Main) and K&S-IF ready for layout.
2024-01-03 Main w/ UI - DRC close.
2024-01-04 Main PCB v1.0 complete.
2024-01-06 Add 3D components for rendering.
2024-01-16 PCBs received.
2024-01-16 Use git lfs for .step files.
2024-01-16 Paddle keying.
2024-04-06 KSInf-MkIII: New JA: Add terminal block
2024-04-14 IF: MKIII. JA: Add terminal block.
2024-04-29 MK-IF-MKIII and JackAdapter PCBs produced.
2024-05-15 Update README.md
    Add Interface info.
2024-07-08 Update manual. Add IF-MkIV.
2024-07-26 KS-MkIV: Pinout for bridge and mini-sounder update.
2024-08-14 MK-IF-MkV
2024-08-14 MK-IF-MkV BOM
2024-08-14 bom clean up
2024-08-16 MK-IF-MkV: Working board.
2024-08-23 Ref manual for MkV Interface.
2024-11-03 MuKOB: rev b, update UI Switch res values to match Scores SW Board.
2025-02-22 Doc: Add auto-detect section
2025-02-22 Doc: Add auto-detect section.
2025-10-02 Update costed BOM
2025-10-20 ProdDocs: Move, rename, remove component docs.
2026-01-15 Update PCB with spare and no 'ears'
2026-01-16 Add FTDI template for SDIF ID
